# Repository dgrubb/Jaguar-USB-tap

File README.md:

# Jaguar USB Tap

The [controller](https://atariage.com/controller_page.html?ControllerID=21&SystemID=JAGUAR) for the [Atari Jaguar](https://en.wikipedia.org/wiki/Atari_Jaguar) game console is a strange beast and doesn't map well to modern controllers (in large part due to the numeric keypad). This makes emulating games on a PC with off-the-shelf controllers, which usually mimic PlayStation or XBox layouts, somewhat cumbersome. One possible solution is to create a device which can convert the Jaguar controller's pinout and signals to a USB HID device.

## Hardware

The hardware was developed using the open-source schematic and PCB design tool [KiCad](http://kicad-pcb.org/). It sports an [STM32F070](http://www.st.com/en/microcontrollers/stm32f070cb.html) ARM Cortex M0 micro-controller which handles input from the Jaguar gamepad and generate appropriate USB HID signalling.

## Accessibility

Even though the design uses entirely surface-mount (SMD) components, with the exception of connectors, I selected components with relatively large footprints such as 1812 for non-polarised capacitors. Larger components resulted in the PCB being bigger than it needs to be, but I feel this to be an acceptable trade-off to ensure that the design is accessible as they require less skill to solder and can also be identified and handled more easily by those with poorer eyesight.

At the heart of the board is an [STM32F070 microcontroller](http://www.st.com/en/microcontrollers/stm32f070cb.html). This part contains an ARM processor core, a USB peripheral and a small handful of GPIO pins making it highly suited as an embedded processor in USB human-interface devices (HID). While the part is a good technical fit for the project there are also accessibility reasons for using an STM32 uC. Chiefly, **firmware can be developed using entirely open-source tools**, such as gcc, on the user’s platform of choice (Linux, Mac OS or, I suppose, even Windows).

## Firmware

### Compatibility

I've tested on:

* Linux
* Windows 7
* MacOS X

In all cases the default USB HID driver on each system is suitable for use with the Jaguar USB Tap and enumerates correctly without additional drivers.

### Building

#### Prerequisites

Requires an ARM toolchain:

* arm-none-eabi-gcc
* arm-none-eabi-gdb
* arm-none-eabi-binutils
* OpenOCD (programming utility)

On Debian/Ubuntu: 

```
$ sudo apt-get install gcc-arm-none-eabi gdb-arm-none-eabi openocd
```
#### Make targets

To build the application:

```
$ make
```

To delete compiled objects and binaries:

```
$ make clean
```

To flash the STM32F0 over STLink:

```
$ make upload
```

To run the debugger, start an OpenOCD session with the target:

```
$ make debug
```

and then, in another terminal window:

```
$ make run_gdb
```

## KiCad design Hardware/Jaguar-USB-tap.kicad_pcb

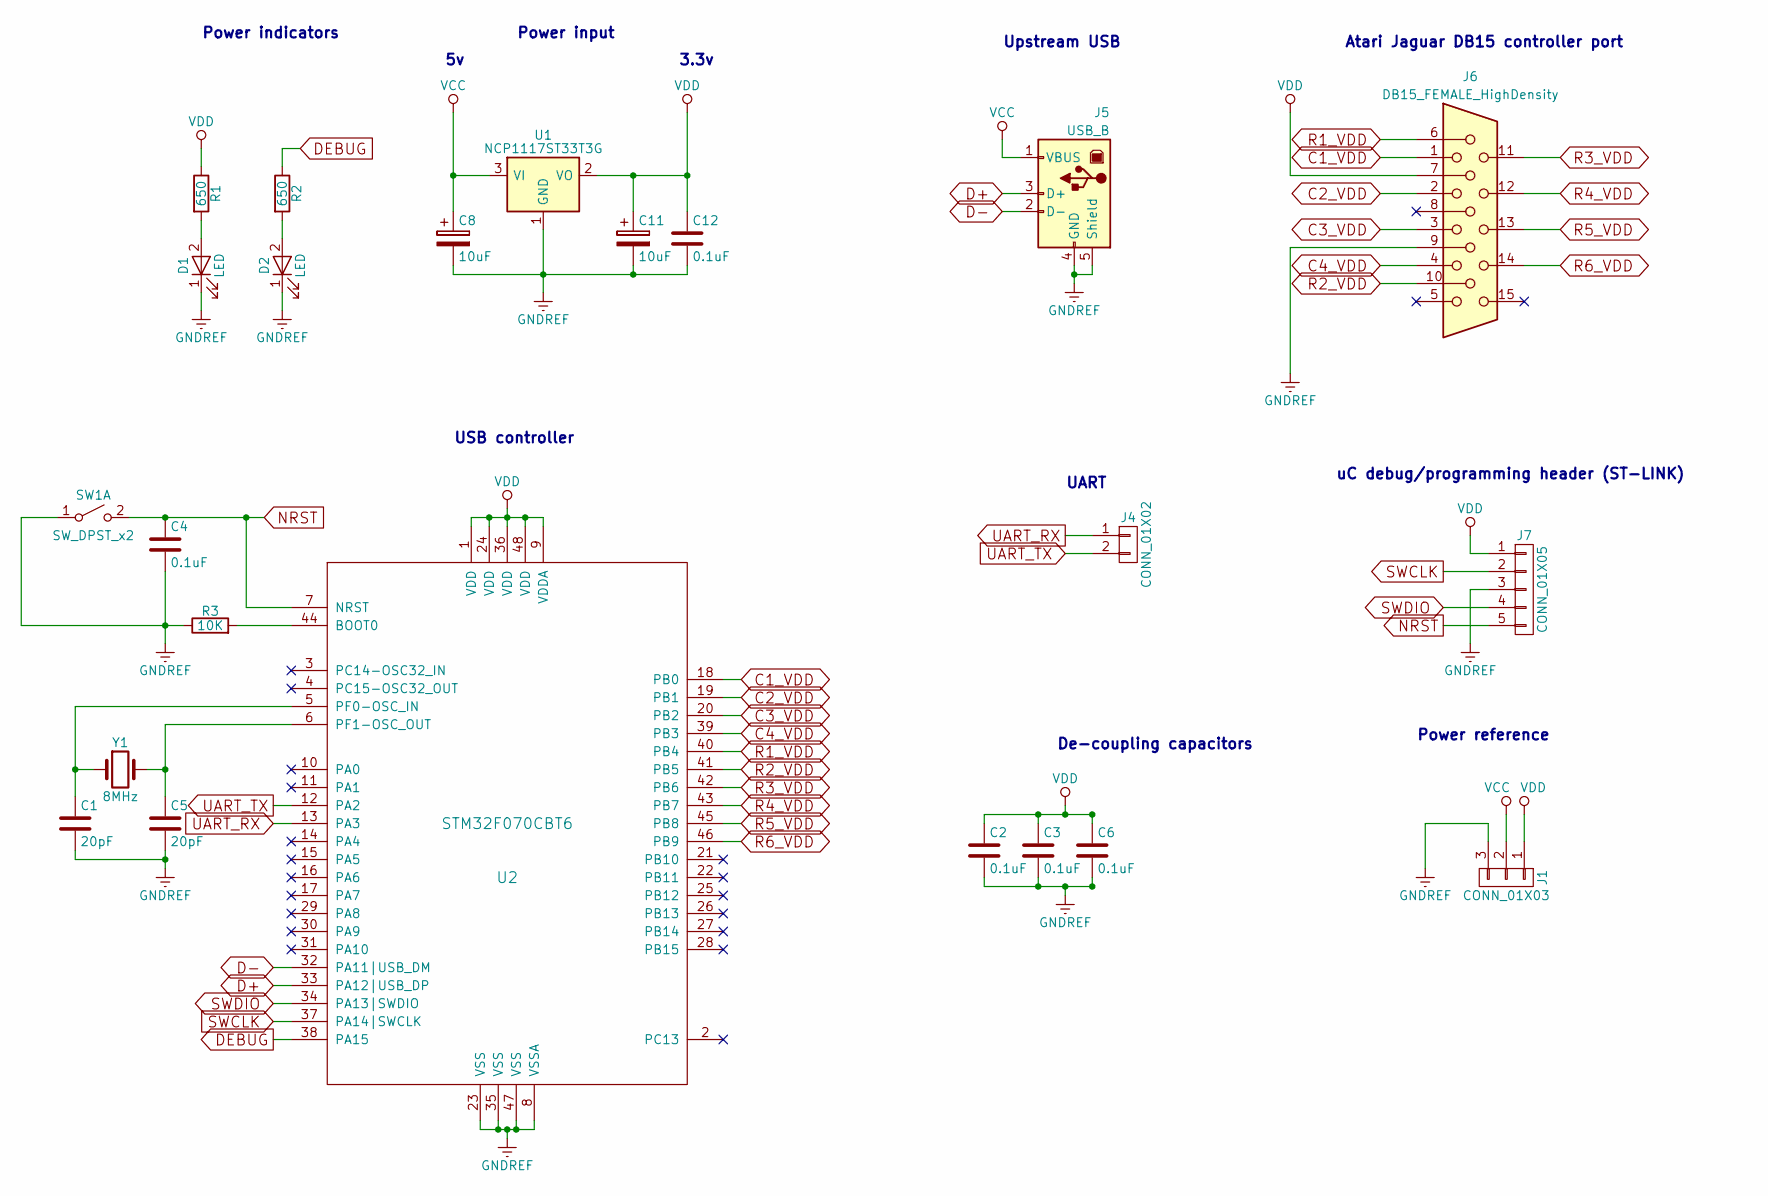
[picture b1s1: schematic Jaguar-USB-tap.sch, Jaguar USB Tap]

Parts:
C1, C5: 20pF; C_1812_HandSoldering
C2, C3, C4, C6, C12: 0.1uF; C_1812_HandSoldering
C8, C11: 10uF; CP_Elec_4x5.8
D1, D2: LED; LED_1206
J1: CONN_01X03; Pin_Header_Straight_1x03_Pitch2.54mm
J4: CONN_01X02; Pin_Header_Straight_1x02_Pitch2.54mm
J5: USB_B
J6: DB15_FEMALE_HighDensity; conn_SPC15430
J7: CONN_01X05; Pin_Header_Straight_1x05_Pitch2.54mm
R1, R2: 650; R_1210_HandSoldering
R3: 10K; R_1210_HandSoldering
SW1: SW_DPST_x2; SW_PUSH_6mm
U1: NCP1117ST33T3G; SOT-223
U2: STM32F070CBT6; LQFP-48_7x7mm_Pitch0.5mm
Y1: 8MHz; Crystal_SMD_HC49-SD_HandSoldering

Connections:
C1_VDD: J6.1, U2.18 (PB0)
C2_VDD: J6.2, U2.19 (PB1)
C3_VDD: J6.3, U2.20 (PB2)
C4_VDD: J6.4, U2.39 (PB3)
D+: J5.3 (D+), U2.33 (PA12|USB_DP)
D-: J5.2 (D-), U2.32 (PA11|USB_DM)
DEBUG: R2.1, U2.38 (PA15)
GNDREF: C1.2, C2.2, C3.2, C4.2, C5.2, C6.2, C8.2, C11.2, C12.2, D1.1 (K), D2.1 (K), J1.3, J5.4 (GND), J5.5 (Shield), J6.9, J7.3, R3.1, SW1.1 (A), U1.1 (GND), U2.8 (VSSA), U2.23 (VSS), U2.35 (VSS), U2.47 (VSS)
NRST: C4.1, J7.5, SW1.2 (B), U2.7 (NRST)
unnamed: C1.1, U2.5 (PF0-OSC_IN), Y1.1
unnamed: C5.1, U2.6 (PF1-OSC_OUT), Y1.2
unnamed: D1.2 (A), R1.2
unnamed: D2.2 (A), R2.2
unnamed: R3.2, U2.44 (BOOT0)
R1_VDD: J6.6, U2.40 (PB4)
R2_VDD: J6.10, U2.41 (PB5)
R3_VDD: J6.11, U2.42 (PB6)
R4_VDD: J6.12, U2.43 (PB7)
R5_VDD: J6.13, U2.45 (PB8)
R6_VDD: J6.14, U2.46 (PB9)
SWCLK: J7.2, U2.37 (PA14|SWCLK)
SWDIO: J7.4, U2.34 (PA13|SWDIO)
UART_RX: J4.1, U2.13 (PA3)
UART_TX: J4.2, U2.12 (PA2)
VCC: C8.1, J1.2, J5.1 (VBUS), U1.3 (VI)
VDD: C2.1, C3.1, C6.1, C11.1, C12.1, J1.1, J6.7, J7.1, R1.1, U1.2 (VO), U2.1 (VDD), U2.9 (VDDA), U2.24 (VDD), U2.36 (VDD), U2.48 (VDD)

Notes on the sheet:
Power indicators
Power input
3.3v
Power reference
Upstream USB
Atari Jaguar DB15 controller port
uC debug/programming header (ST-LINK)
UART
De-coupling capacitors
USB controller

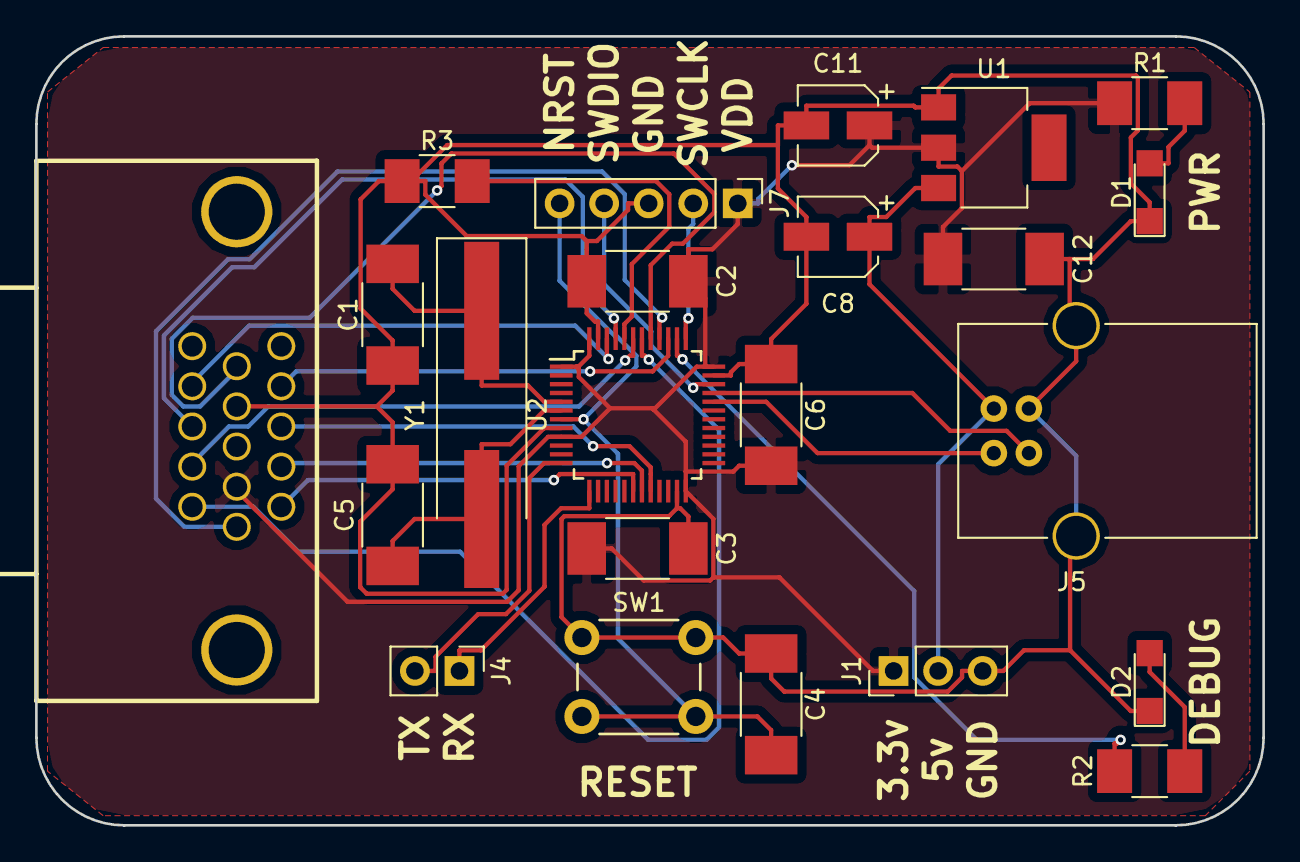
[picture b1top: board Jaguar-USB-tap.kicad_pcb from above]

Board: 2 copper layers, 70.0 x 45.0 mm, 23 parts (0 on the bottom side), 26 nets.

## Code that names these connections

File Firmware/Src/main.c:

#include <string.h>
#include "main.h"
#include "stm32f0xx_hal.h"
#include "usb_device.h"
#include "jaguar/jaguar-controller.h"

static char welcome_message[] = "\n\r"
"\n\r"
"            Jaguar-USB-tap\n\r"
"            --------------\n\r"
"\n\r"
"         by David Grubb, 2018\n\r"
"  https://github.com/dgrubb/Jaguar-USB-tap\n\r"
"\n\r"
"A USB adapter for the Atari Jaguar controller.\n\r"
"\n\r"
"            Welcome to 1993!\n\r";

UART_HandleTypeDef huart2;

void SystemClock_Config(void);
static void MX_GPIO_Init(void);
static void MX_USART2_UART_Init(void);

int main(void)
{
    /* Reset of all peripherals, Initializes the Flash interface and the Systick. */
    HAL_Init();

    /* Configure the system clock */
    SystemClock_Config();

    /* Initialize all configured peripherals */
    MX_GPIO_Init();
    MX_USART2_UART_Init();
    MX_USB_DEVICE_Init();

    /* Turn on the DEBUG LED for visual indication that we're up and running and
     * display a welcome message on the UART 
     * */
    HAL_GPIO_WritePin(GPIOA, GPIO_PIN_15, GPIO_PIN_SET);
    HAL_UART_Transmit(&huart2, (uint8_t *)welcome_message, strlen(welcome_message), HAL_MAX_DELAY);

    /* Infinite loop */
    while (1) {
        jaguar_update_inputs(&huart2);
    }
}

void systick_init()
{
    (void) SysTick_Config (HAL_RCC_GetSysClockFreq()/1000);
}

void SystemClock_Config(void)
{
    RCC_OscInitTypeDef RCC_OscInitStruct;
    RCC_ClkInitTypeDef RCC_ClkInitStruct;
    RCC_PeriphCLKInitTypeDef PeriphClkInit;

    /* Use the external 8MHz crystal (HSE) and multiply it
     * by 6 for a resulting core frequency of 48MHz.
     */
    RCC_OscInitStruct.OscillatorType = RCC_OSCILLATORTYPE_HSE;
    RCC_OscInitStruct.HSEState = RCC_HSE_ON;
    RCC_OscInitStruct.PLL.PLLState = RCC_PLL_ON;
    RCC_OscInitStruct.PLL.PLLSource = RCC_PLLSOURCE_HSE;
    RCC_OscInitStruct.PLL.PLLMUL = RCC_PLL_MUL6;
    RCC_OscInitStruct.PLL.PREDIV = RCC_PREDIV_DIV1;
    if (HAL_RCC_OscConfig(&RCC_OscInitStruct) != HAL_OK) {
        _Error_Handler(__FILE__, __LINE__);
    }

    RCC_ClkInitStruct.ClockType = RCC_CLOCKTYPE_HCLK   |
                                  RCC_CLOCKTYPE_SYSCLK |
                                  RCC_CLOCKTYPE_PCLK1;
    RCC_ClkInitStruct.SYSCLKSource = RCC_SYSCLKSOURCE_PLLCLK;
    RCC_ClkInitStruct.AHBCLKDivider = RCC_SYSCLK_DIV1;
    RCC_ClkInitStruct.APB1CLKDivider = RCC_HCLK_DIV1;

    if (HAL_RCC_ClockConfig(&RCC_ClkInitStruct, FLASH_LATENCY_1) != HAL_OK) {
        _Error_Handler(__FILE__, __LINE__);
    }

    /* Enable the USB clock and drive it from the multiplied external
     * oscillator. The external crystal is necessary for consistency at high-speeds,
     * otherwise drift will cause oddities on the USB clock rate.
     */
    PeriphClkInit.PeriphClockSelection = RCC_PERIPHCLK_USB;
    PeriphClkInit.UsbClockSelection = RCC_USBCLKSOURCE_PLL;

    if (HAL_RCCEx_PeriphCLKConfig(&PeriphClkInit) != HAL_OK) {
        _Error_Handler(__FILE__, __LINE__);
    }

    HAL_SYSTICK_Config(HAL_RCC_GetHCLKFreq()/1000);
    HAL_SYSTICK_CLKSourceConfig(SYSTICK_CLKSOURCE_HCLK);
    HAL_NVIC_SetPriority(SysTick_IRQn, 0, 0);
}

static void MX_USART2_UART_Init(void)
{
    /*
     * TX: Pin PA2
     * RX: Pin PA3
     *
     * UART settings (PuTTY, Minicom etc):
     *
     * Baud: 152000
     * Data len: 8 bits
     * Stop bit: 1
     * No hardware control.
     */
    huart2.Instance = USART2;
    huart2.Init.BaudRate = 115200;
    huart2.Init.WordLength = UART_WORDLENGTH_8B;
    huart2.Init.StopBits = UART_STOPBITS_1;
    huart2.Init.Parity = UART_PARITY_NONE;
    huart2.Init.Mode = UART_MODE_TX_RX;
    huart2.Init.HwFlowCtl = UART_HWCONTROL_NONE;
    huart2.Init.OverSampling = UART_OVERSAMPLING_16;
    huart2.Init.OneBitSampling = UART_ONE_BIT_SAMPLE_DISABLE;
    huart2.AdvancedInit.AdvFeatureInit = UART_ADVFEATURE_NO_INIT;
    if (HAL_UART_Init(&huart2) != HAL_OK) {
        _Error_Handler(__FILE__, __LINE__);
    }
}

static void MX_GPIO_Init(void)
{
    GPIO_InitTypeDef GPIO_InitStruct;

    /* GPIO Ports Clock Enable */
    __HAL_RCC_GPIOF_CLK_ENABLE();
    __HAL_RCC_GPIOA_CLK_ENABLE();
    __HAL_RCC_GPIOB_CLK_ENABLE();

    /*Configure GPIO pin Output Level */
    HAL_GPIO_WritePin(GPIOA, GPIO_PIN_15, GPIO_PIN_RESET);

    /* Pins PB0 through PB3 are used as ouputs for setting the 
     * address lines of the Jaguar controller.
     */
    GPIO_InitStruct.Pin = GPIO_PIN_0 | GPIO_PIN_1 | GPIO_PIN_2 | GPIO_PIN_3;
    GPIO_InitStruct.Mode = GPIO_MODE_OUTPUT_PP;
    GPIO_InitStruct.Pull = GPIO_PULLUP;
    GPIO_InitStruct.Speed = GPIO_SPEED_FREQ_LOW;
    HAL_GPIO_Init(GPIOB, &GPIO_InitStruct);

    /* Pins PB4 through PB9 are set as inputs for reading the
     * button states of those buttons assigned to the selected address.
     */
    GPIO_InitStruct.Pin = GPIO_PIN_4 | GPIO_PIN_5 | GPIO_PIN_6 |
                          GPIO_PIN_7 | GPIO_PIN_8 | GPIO_PIN_9;
    GPIO_InitStruct.Mode = GPIO_MODE_INPUT;
    GPIO_InitStruct.Pull = GPIO_NOPULL;
    HAL_GPIO_Init(GPIOB, &GPIO_InitStruct);

    /* Setup pin PA15, connected to the LED labelled DEBUG on the silkscreen, as
     * an output.
     */
    GPIO_InitStruct.Pin = GPIO_PIN_15;
    GPIO_InitStruct.Mode = GPIO_MODE_OUTPUT_PP;
    GPIO_InitStruct.Pull = GPIO_NOPULL;
    GPIO_InitStruct.Speed = GPIO_SPEED_FREQ_LOW;
    HAL_GPIO_Init(GPIOA, &GPIO_InitStruct);
}

void _Error_Handler(char * file, int line)
{
    while(1) {}
}

#ifdef USE_FULL_ASSERT

void assert_failed(uint8_t* file, uint32_t line)
{
}

#endif

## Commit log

2017-11-20 Add skeleton of project structure.
2017-11-20 Add a new part library to include our chosen uC device (STM32F070F6P6).
2017-11-20 Progress on hardware piece.
    1) Add documenation for TI logic level shifter.
    2) Finish up initial schematic.
    3) Add clear .pdf before adding component footprints.
    4) Add libraries for TI logic level shifter.
2017-11-20 Add a preview image for casual inspection.
2017-11-20 Add PCB work.
    1) Add footprints for TSSOP16 and TSSOP20 devices.
    2) Create a PCB layout for adapter and board cut.
2017-11-20 Add a preview of the board itself.
2017-11-20 Add traces and fill zones to PCB.
2017-11-20 Add Gerbers for producing boards.
2017-11-20 Add a BOM spreadsheet with pricing from DigiKey.
2017-11-20 Move BOM into its own directory and export a pdf for convenience.
2017-11-20 Add an Atari/Jaguar logo.
2017-11-21 Add a smaller version of the rendered board.
2017-11-21 Add ST and ARM components (CMSIS and HAl drivers).
2017-11-21 Circuit improvements.
    1) Add an indicator LED to OE.
    2) Add a capacitor to NRST.
2017-11-21 Add reference manual for target platform.
2017-11-21 Minor tweaks for PCB layout positioning of components.
2017-11-21 Update Gerbers and drill files to reflect tweaks to schematic.
2017-11-21 Add ST USB device library.
2017-11-21 Add more documentation specific for this project.
2017-11-21 Add HAL configuration, requires some pruning!
2017-11-21 Add a Makefile template.
2017-11-21 Add a linker script.
2017-11-28 Update silkscreen artwork.
2017-11-28 Add updated gerber files.
2017-11-30 Rework startup routines and linker script.
2017-11-30 Add a proper linker script and configure startup.
2017-11-30 Simplify project skeleton.
2017-11-30 Clean project.
2017-11-30 Cleanup main.c
2017-11-30 Add some code for initialising GPIO.
2017-11-30 Fix minor formatting inconsistencies in Makefile.
2017-11-30 Lay out peripheral directories
2017-11-30 Create a compilation module for GPIO handling.
2017-11-30 Add further work on reading input states.
2017-11-30 Add compilation module for Jaguar related items.
2017-11-30 Add standard file headers to Jaguar controller module.
2017-11-30 Add some function prototypes to Jaguar controller.
2017-12-01 Add a button mapping type to identify what address/data pins belong to which controller buttons.
2017-12-01 Add a pin mapping between the DB15 socket and the uCs PA port.
2017-12-01 Add logic for sweeping GPIO for reading gamepad state.
2017-12-01 Add mapping for physical uC port and abstracted type.
2017-12-01 Add placeholder for USB messaging.
2017-12-01 Remove dead code.
2017-12-01 Add Jaguar controller sweep to main program logic.
2017-12-01 Enable pin PB1 for output.
2017-12-02 Fix pointer references to GPIO port.
2017-12-05 Turn on a test pin on bootup (this is tied to an LED).
2017-12-08 Add image of an assembled board and blank PCBs.
2017-12-08 Change OpenOCD configuration to explicitly target our ST-LINK and STM32F07 parts, rather than relying on a Nucleo wrapper.
2017-12-08 Minor tweaks to Makefile to allow for easier debugging.
2017-12-12 Dramatic change of tact: remove hand-rolled handlers and startup definitions in favour of those generated by STM32CubeMX.
2017-12-21 Rework schematic to fx hardware bugs and add features.
    1) Add jumpers for OE to allow manual disabling of logic-level translator ICs.
    2) Add RESET button.
    3) Upgrade to larger STM32F07 series IC so ST-LINK SWD lines don't have to pull double-duty as general-purpose GPIO. Allows for continued debugging during operation.
    4) Fix missing pin assignments in previous board which prevented proper powerng of uC.
2017-12-21 Start PCB layout of revised board.
2017-12-22 Finish up PCB layout with traces and zone pours.
2018-01-04 Switch target uC from STM32F070RB to STM32F070CBT6.
2018-01-05 Re-allocate button mapping according to pin mapping for 0.2 rev board.
2018-01-05 Update USB descriptor strings.
2018-01-05 Progress due to testing with actual hardware.
    1) Enable some basic serial debugging.
    2) Rewrite pin reading functions according to gained knowledge about how the controller addresses buttons.
2018-01-10 Remove logic-level translation ICs and drive teh controller at 3.3v directly from the uC.
2018-01-19 Remove accidental swap file commit.
2018-01-19 Cleanup code for readability and add annotations.
2018-01-19 Add an ASCII art based welcome message to UART on startup.
2018-01-22 Create LICENSE
2018-01-22 Update USB to send gamepad information.
2018-01-22 Slightly realign report descriptor.
2018-01-22 Ensure we have enough bits to send all button states.
2018-01-22 Start work on sending a Jaguar-specific report over USB.
2018-01-22 Add some more USB report packaging stuff.
2018-01-23 Continue experiments with USB reports.
2018-01-23 Finally! Messy code, but fully working.
2018-01-23 Cleanup code ofr efficiency and readability.
2018-01-24 Remove old BOMs.
2018-01-24 Add updated BOM.
2018-01-24 Remove Atari branding and replace with OSHW logo instead.
2018-01-24 Remove old renderings.
2018-01-24 Add new renderings.
2018-01-24 Add new pictures of revised board.
2018-01-24 Remove old schematics.
2018-01-24 Add PDF schematic.
2018-01-24 Remove cool Atari ASCII art.
2018-01-24 Cast string before sending over UART to silence compiler warning.
2018-01-24 Ensure correct pointer type when dispatching USB message.
2018-01-25 Add some nicer pictures.
2018-01-25 Add a shiny new VID/PID, courtesy of pid.codes
2018-01-25 Switch debug flag off and remove an out-dated comment.
2018-01-30 Correct VID/PID pair by changing to base-16 in code.
